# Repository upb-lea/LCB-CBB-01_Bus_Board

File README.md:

# Bus board LCB-CBB-01 for the LEA control board

This is the dock extension board for the LEA control board LCB-CCB-01. Please refer to the [LCB-CCB-01 repository](https://github.com/upb-lea/LCB-CCB-01_LEA_Control_Board) for a PCB and project overview.

Note, that you also need to install the `LEA KiCad Library` to view this PCB in this repository. To do this, follow the instructions mentioned [here](https://github.com/upb-lea/LCB-CCB-01_LEA_Control_Board/blob/main/README.md#downloading-this-project-and-folder-structure).

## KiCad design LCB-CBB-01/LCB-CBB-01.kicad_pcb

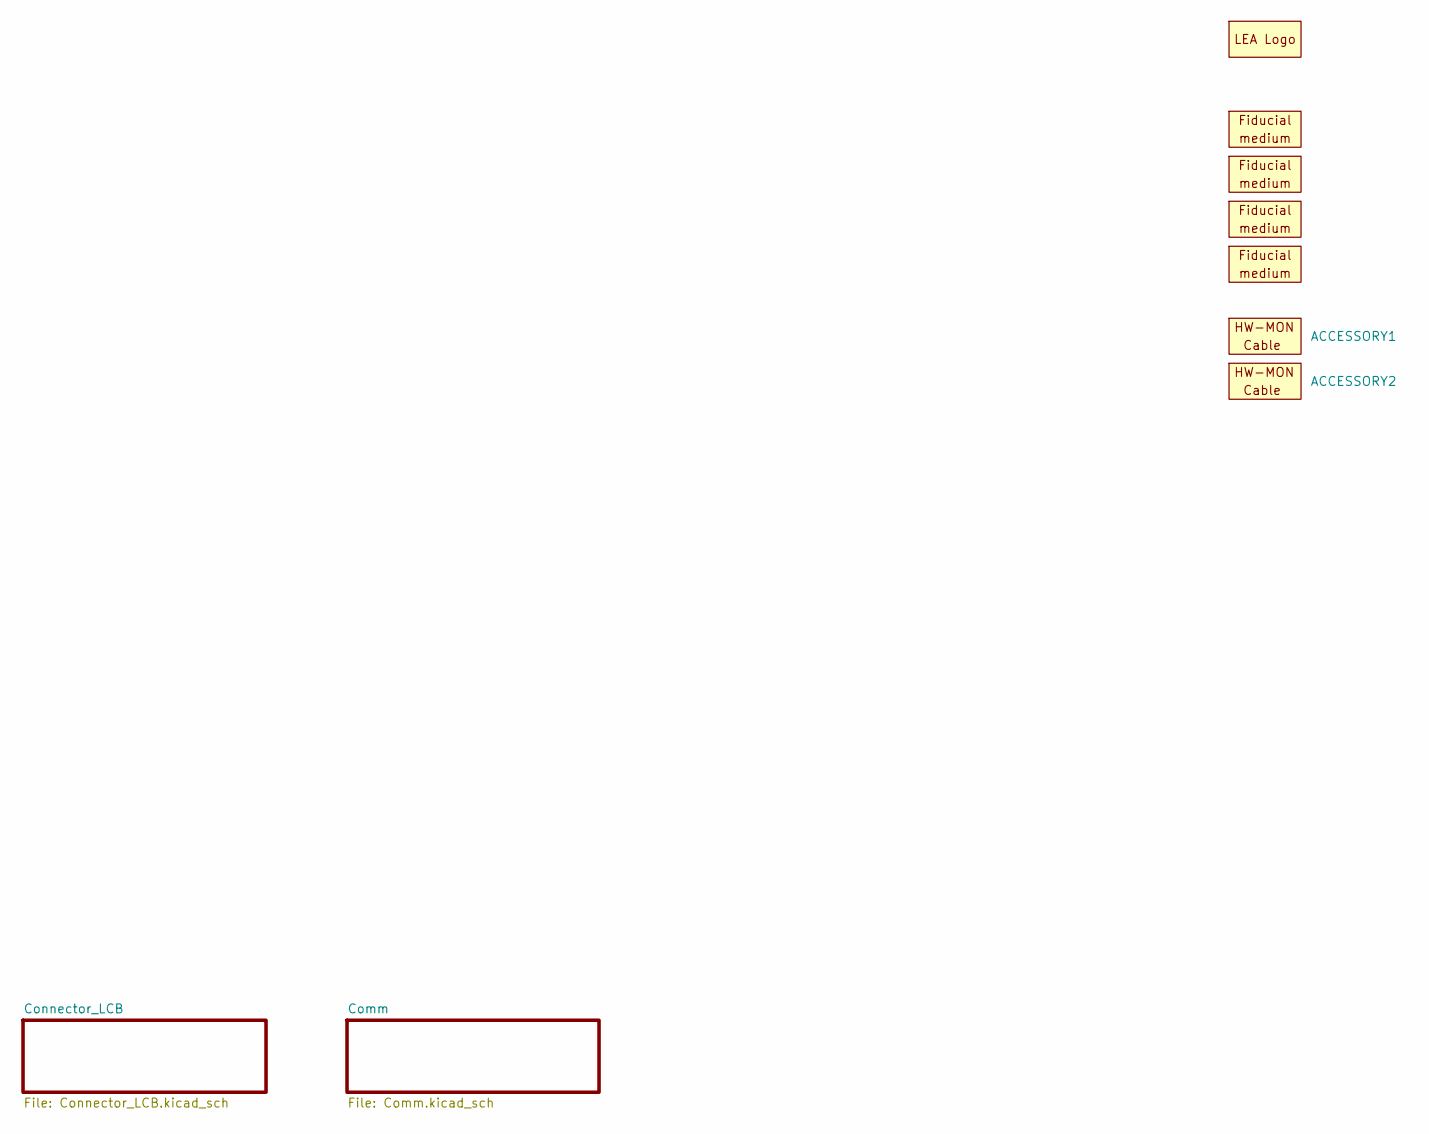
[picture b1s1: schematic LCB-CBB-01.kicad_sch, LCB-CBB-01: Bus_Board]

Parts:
ACCESSORY1, ACCESSORY2: ACCESSORY_BusBoard_SPI_Cable; mouser# 538-15134-0805
O1, O2, O3, O4: Fiducial_medium; Fiducials_medium
SYM1: SYM_LEA_Logo; SYM_lea_logo

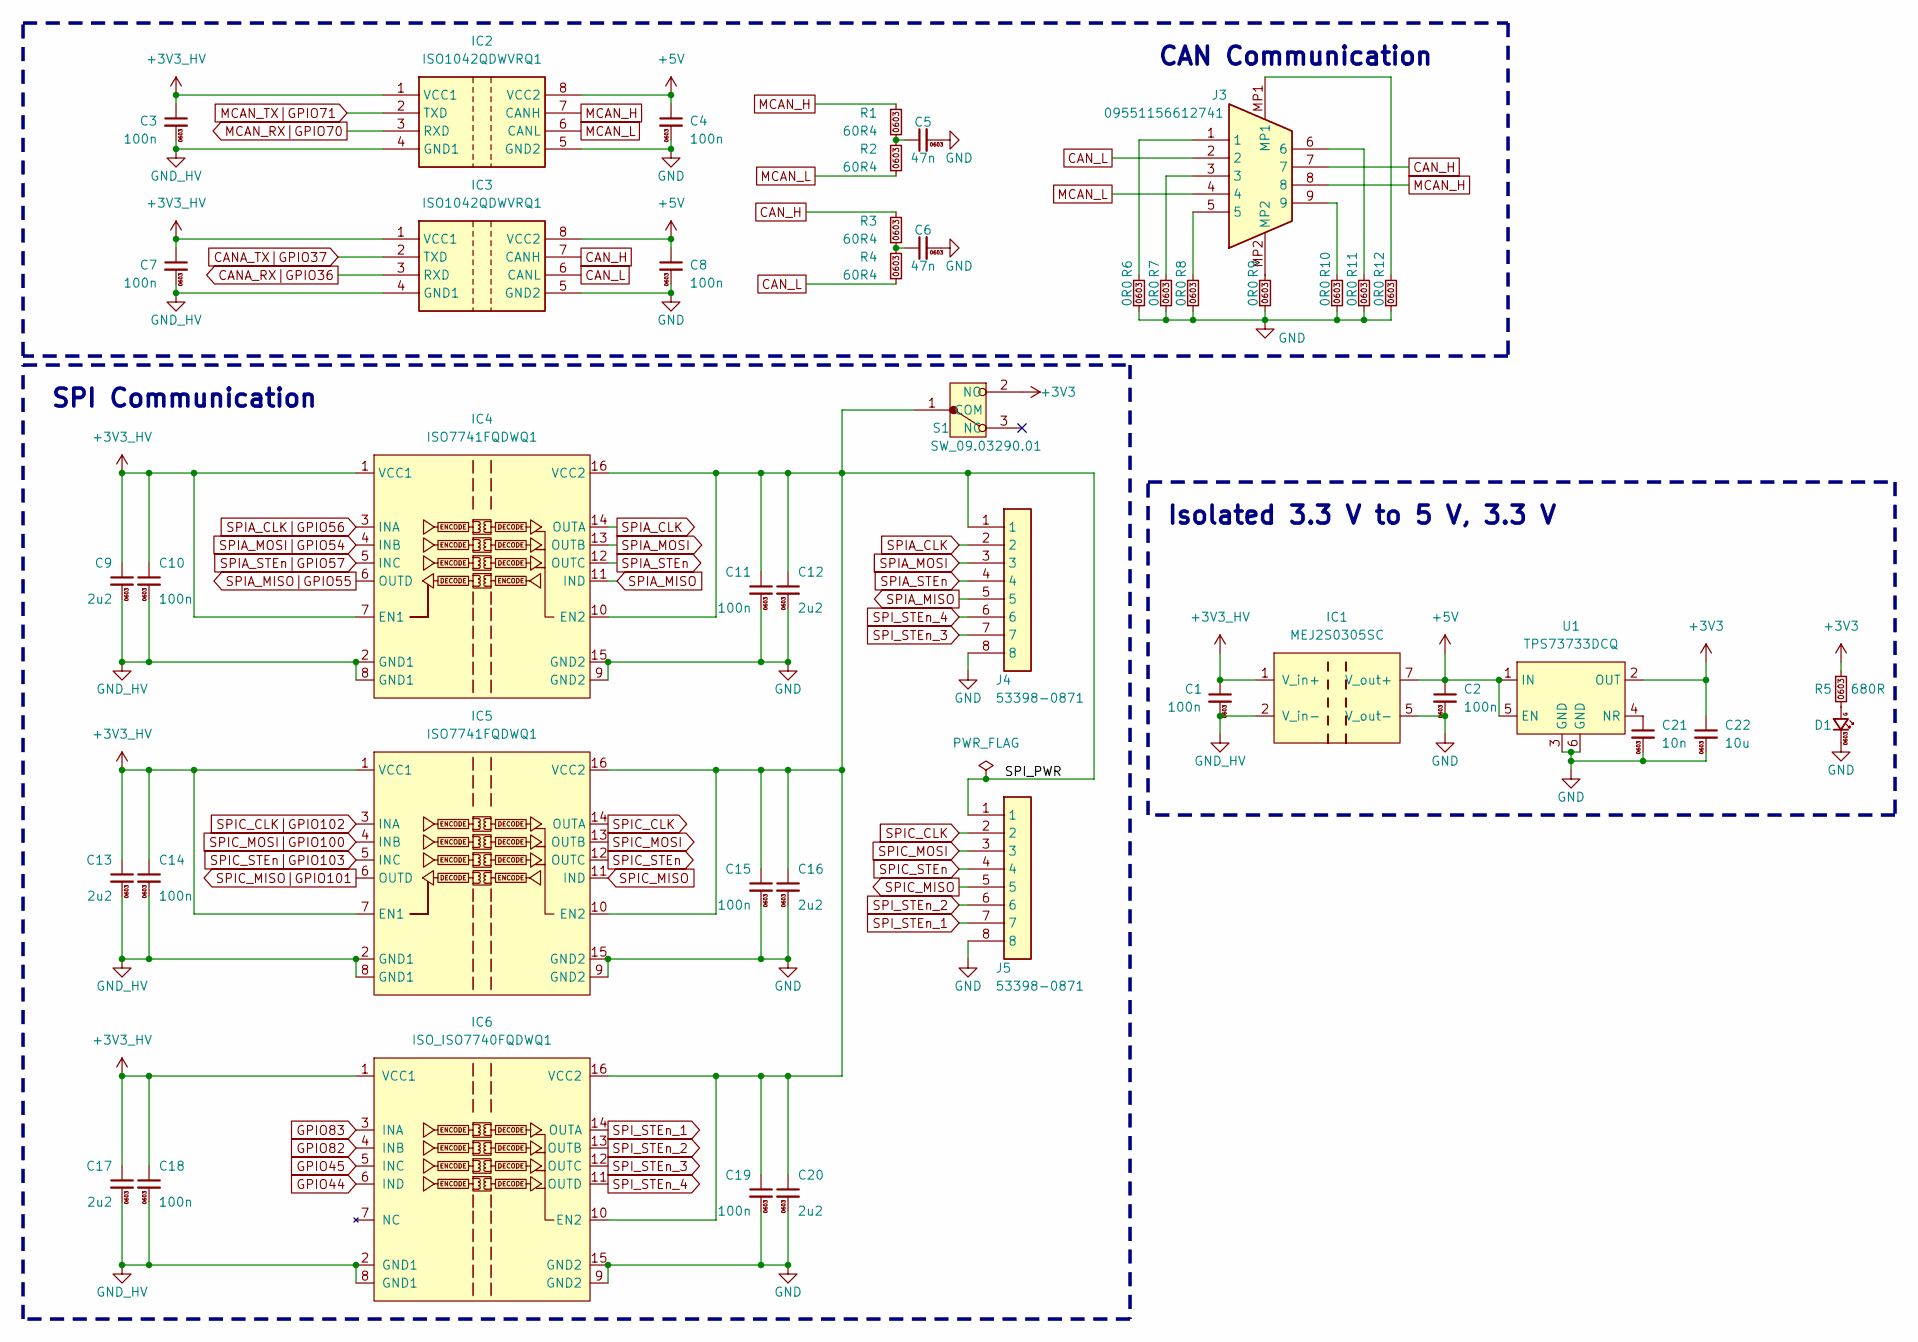
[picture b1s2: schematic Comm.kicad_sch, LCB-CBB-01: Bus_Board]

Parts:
C1, C2, C3, C4, C7, C8, C10, C11, C14, C15, C18, C19: 100n; C_0603; mouser# 810-C1608X5R1H104K
C5, C6: 47n; C_0603; mouser# 81-GCM188R71H473K55D
C9, C12, C13, C16, C17, C20: 2u2; C_0603; mouser# 810-C1608X5R1V225K
C21: 10n; C_0603; mouser# 810-CGA3E2X7R1H103K
C22: 10u; C_0603; mouser# 81-GRM188R61E106KA3D
D1: 2mA; LED_0603_G; mouser# 604-APTD1608LCGCK
IC1: MEJ2S0305SC; SIP-7_Murata_MEJ1S0305SC; mouser# 580-MEJ2S0305SC
IC2, IC3: ISO1042QDWVRQ1; SOIC127P1150X280-8N; mouser# 595-ISO1042QDWVRQ1
IC4, IC5: ISO7741FQDWQ1; SOIC127P1030X265-16N; mouser# 595-ISO7741FQDWQ1
IC6: ISO_ISO7740FQDWQ1; SOIC127P1030X265-16N; mouser# 595-ISO7740FQDWQ1
J3: 09551156612741; Conn_Sub-D_09551156612741; mouser# 617-09551156612741
J4, J5: 53398-0871; Conn_Molex_533980871; mouser# 538-53398-0871
R1, R2, R3, R4: 60R4; R_0603; mouser# 755-ESR03EZPD60R4
R5: 680R; R_0603; mouser# 71-CRCW0603680RFKEAC
R6, R7, R8, R9, R10, R11, R12: 0R0; R_0603; mouser# 71-CRCW06030000Z0EAC
S1: SW_09.03290.01; 090329001; mouser# 123-09.03290.01
U1: TPS73733DCQ; SOT-223-6_TI; mouser# 595-TPS73733DCQG4

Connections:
+3V3: C22.1, R5.1, S1.2 (NO), U1.2 (OUT)
+3V3_Connector_HV: C1.1, C3.1, C7.1, C9.1, C10.1, C13.1, C14.1, C17.1, C18.1, IC1.1 (V_in+), IC2.1 (VCC1), IC3.1 (VCC1), IC4.1 (VCC1), IC4.7 (EN1), IC5.1 (VCC1), IC5.7 (EN1), IC6.1 (VCC1); also elsewhere on the board
+5V: C2.1, C4.1, C8.1, IC1.7 (V_out+), IC2.8 (VCC2), IC3.8 (VCC2), U1.1 (IN), U1.5 (EN)
/Comm/SPI_PWR: C11.1, C12.1, C15.1, C16.1, C19.1, C20.1, IC4.10 (EN2), IC4.16 (VCC2), IC5.10 (EN2), IC5.16 (VCC2), IC6.10 (EN2), IC6.16 (VCC2), J4.1, J5.1, S1.1 (COM)
CANA_RX|GPIO36: IC3.3 (RXD); also elsewhere on the board
CANA_TX|GPIO37: IC3.2 (TXD); also elsewhere on the board
CAN_H: IC3.7 (CANH), J3.7, R3.2
CAN_L: IC3.6 (CANL), J3.2, R4.1
GND: C2.2, C4.2, C5.2, C6.2, C8.2, C11.2, C12.2, C15.2, C16.2, C19.2, C20.2, C21.2, C22.2, D1.C, IC1.5 (V_out-), IC2.5 (GND2), IC3.5 (GND2), IC4.9 (GND2), IC4.15 (GND2), IC5.9 (GND2), IC5.15 (GND2), IC6.9 (GND2), IC6.15 (GND2), J4.8, J5.8, R6.1, R7.1, R8.1, R9.1, R10.1, R11.1, R12.1, U1.3 (GND), U1.6 (GND)
GND_HV: C1.2, C3.2, C7.2, C9.2, C10.2, C13.2, C14.2, C17.2, C18.2, IC1.2 (V_in-), IC2.4 (GND1), IC3.4 (GND1), IC4.2 (GND1), IC4.8 (GND1), IC5.2 (GND1), IC5.8 (GND1), IC6.2 (GND1), IC6.8 (GND1); also elsewhere on the board
GPIO44: IC6.6 (IND); also elsewhere on the board
GPIO45: IC6.5 (INC); also elsewhere on the board
GPIO82: IC6.4 (INB); also elsewhere on the board
GPIO83: IC6.3 (INA); also elsewhere on the board
MCAN_H: IC2.7 (CANH), J3.8, R1.2
MCAN_L: IC2.6 (CANL), J3.4, R2.1
MCAN_RX|GPIO70: IC2.3 (RXD); also elsewhere on the board
MCAN_TX|GPIO71: IC2.2 (TXD); also elsewhere on the board
unnamed: C5.1, R1.1, R2.2
unnamed: C6.1, R3.1, R4.2
unnamed: D1.A, R5.2
unnamed: J3.1, R6.2
unnamed: J3.3, R7.2
unnamed: J3.5, R8.2
unnamed: J3.6, R11.2
unnamed: J3.9, R10.2
unnamed: J3.MP1, R12.2
unnamed: J3.MP2, R9.2
unnamed: C21.1, U1.4 (NR)
SPIA_CLK: IC4.14 (OUTA), J4.2
SPIA_CLK|GPIO56: IC4.3 (INA); also elsewhere on the board
SPIA_MISO: IC4.11 (IND), J4.5
SPIA_MISO|GPIO55: IC4.6 (OUTD); also elsewhere on the board
SPIA_MOSI: IC4.13 (OUTB), J4.3
SPIA_MOSI|GPIO54: IC4.4 (INB); also elsewhere on the board
SPIA_STEn: IC4.12 (OUTC), J4.4
SPIA_STEn|GPIO57: IC4.5 (INC); also elsewhere on the board
SPIC_CLK: IC5.14 (OUTA), J5.2
SPIC_CLK|GPIO102: IC5.3 (INA); also elsewhere on the board
SPIC_MISO: IC5.11 (IND), J5.5
SPIC_MISO|GPIO101: IC5.6 (OUTD); also elsewhere on the board
SPIC_MOSI: IC5.13 (OUTB), J5.3
SPIC_MOSI|GPIO100: IC5.4 (INB); also elsewhere on the board
SPIC_STEn: IC5.12 (OUTC), J5.4
SPIC_STEn|GPIO103: IC5.5 (INC); also elsewhere on the board
SPI_STEn_1: IC6.14 (OUTA), J5.7
SPI_STEn_2: IC6.13 (OUTB), J5.6
SPI_STEn_3: IC6.12 (OUTC), J4.7
SPI_STEn_4: IC6.11 (OUTD), J4.6

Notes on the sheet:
CAN Communication
SPI Communication
Isolated 3.3 V to 5 V, 3.3 V

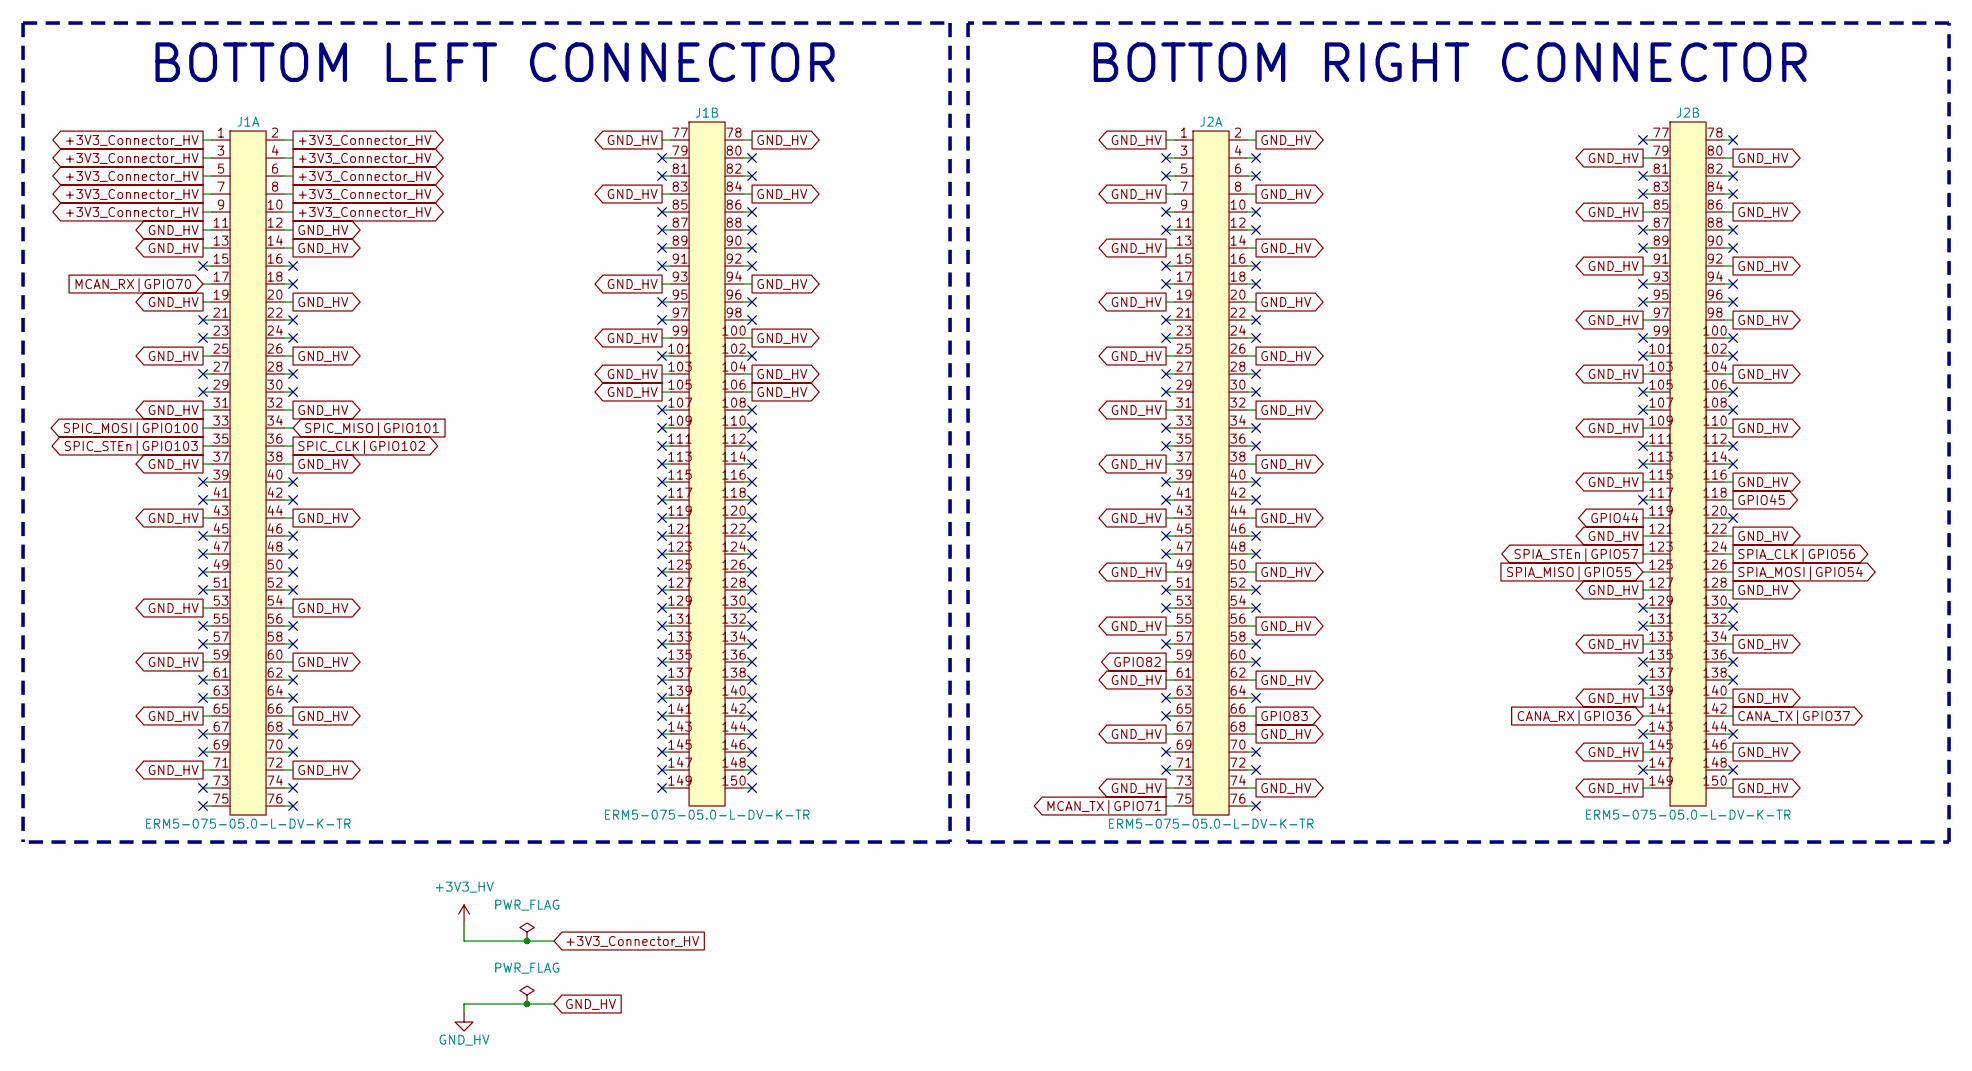
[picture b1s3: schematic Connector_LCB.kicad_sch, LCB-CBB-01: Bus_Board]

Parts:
J1, J2: ERM5-075-05.0-L-DV-K-TR; ERM5-075-05.0-L-DV; mouser# 200-ERM5075050LDVKTR; Mouser No 200-ERM5075050LDVKTR

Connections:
+3V3_Connector_HV: J1.1, J1.2, J1.3, J1.4, J1.5, J1.6, J1.7, J1.8, J1.9, J1.10; also elsewhere on the board
CANA_RX|GPIO36: J2.141; also elsewhere on the board
CANA_TX|GPIO37: J2.142; also elsewhere on the board
GND_HV: J1.11, J1.12, J1.13, J1.14, J1.19, J1.20, J1.25, J1.26, J1.31, J1.32, J1.37, J1.38, J1.43, J1.44, J1.53, J1.54, J1.59, J1.60, J1.65, J1.66, J1.71, J1.72, J1.77, J1.78, J1.83, J1.84, J1.93, J1.94, J1.99, J1.100, J1.103, J1.104, J1.105, J1.106, J2.1, J2.2, J2.7, J2.8, J2.13, J2.14, J2.19, J2.20, J2.25, J2.26, J2.31, J2.32, J2.37, J2.38, J2.43, J2.44, J2.49, J2.50, J2.55, J2.56, J2.61, J2.62, J2.67, J2.68, J2.73, J2.74, J2.79, J2.80, J2.85, J2.86, J2.91, J2.92, J2.97, J2.98, J2.103, J2.104, J2.109, J2.110, J2.115, J2.116, J2.121, J2.122, J2.127, J2.128, J2.133, J2.134, J2.139, J2.140, J2.145, J2.146, J2.149, J2.150; also elsewhere on the board
GPIO44: J2.119; also elsewhere on the board
GPIO45: J2.118; also elsewhere on the board
GPIO82: J2.59; also elsewhere on the board
GPIO83: J2.66; also elsewhere on the board
MCAN_RX|GPIO70: J1.17; also elsewhere on the board
MCAN_TX|GPIO71: J2.75; also elsewhere on the board
SPIA_CLK|GPIO56: J2.124; also elsewhere on the board
SPIA_MISO|GPIO55: J2.125; also elsewhere on the board
SPIA_MOSI|GPIO54: J2.126; also elsewhere on the board
SPIA_STEn|GPIO57: J2.123; also elsewhere on the board
SPIC_CLK|GPIO102: J1.36; also elsewhere on the board
SPIC_MISO|GPIO101: J1.34; also elsewhere on the board
SPIC_MOSI|GPIO100: J1.33; also elsewhere on the board
SPIC_STEn|GPIO103: J1.35; also elsewhere on the board

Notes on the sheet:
BOTTOM LEFT CONNECTOR
BOTTOM RIGHT CONNECTOR

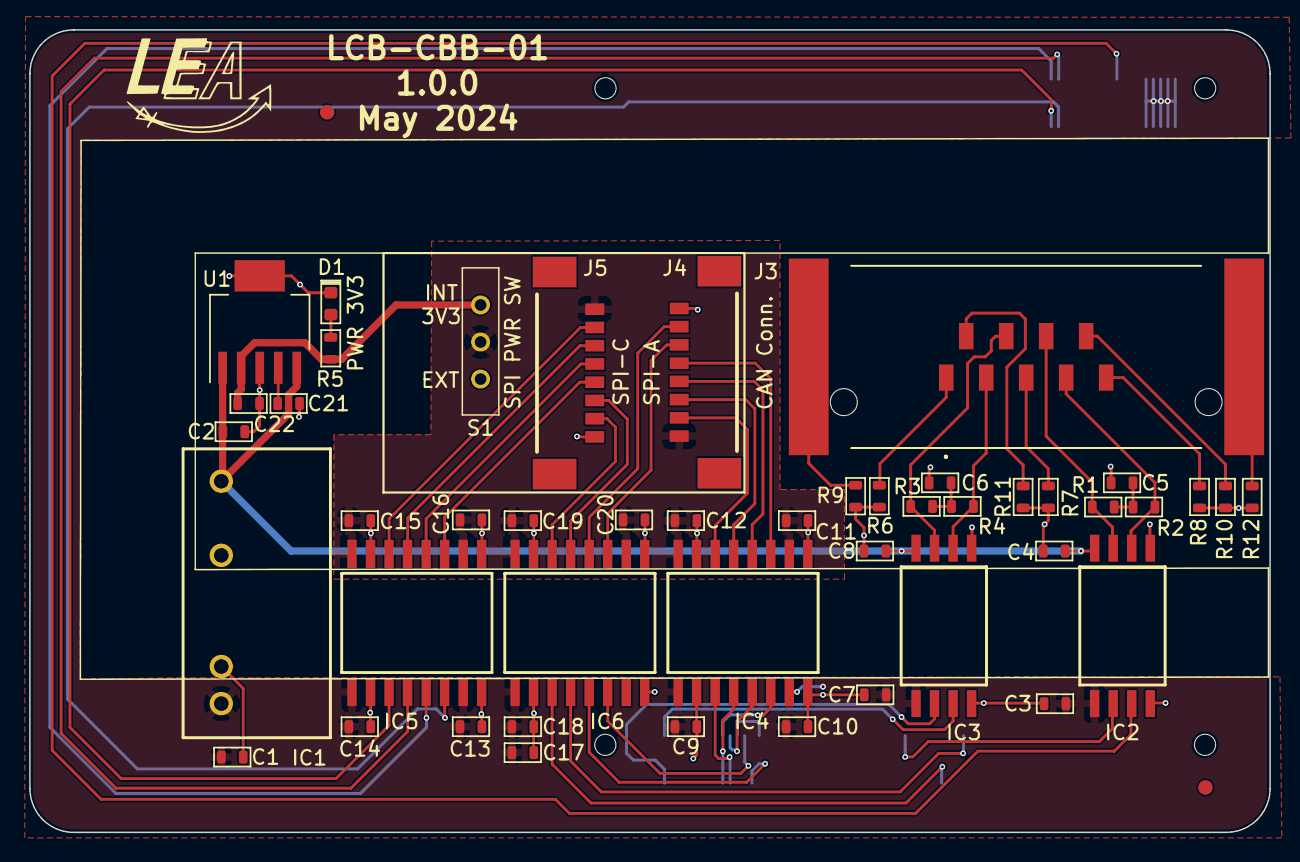
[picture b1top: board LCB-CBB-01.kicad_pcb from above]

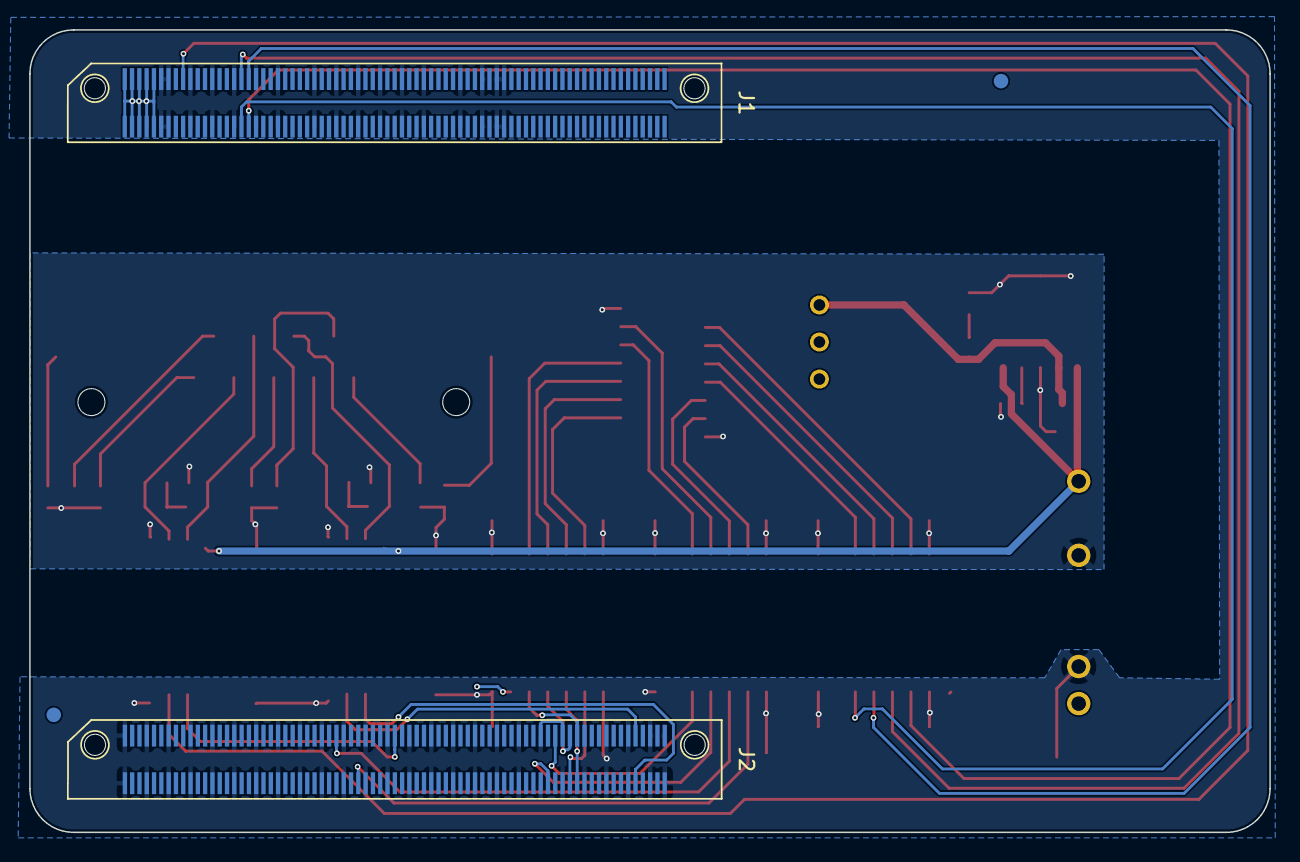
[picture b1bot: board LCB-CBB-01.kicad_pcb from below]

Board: 2 copper layers, 85.0 x 55.0 mm, 53 parts (4 on the bottom side), 49 nets.

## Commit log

2024-04-26 set up project structure
2024-05-16 update to kicad 8, subd connector update
2024-05-18 bump version to 1.0.0
